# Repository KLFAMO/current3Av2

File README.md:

# current3Av2
Current driver for compensating coils

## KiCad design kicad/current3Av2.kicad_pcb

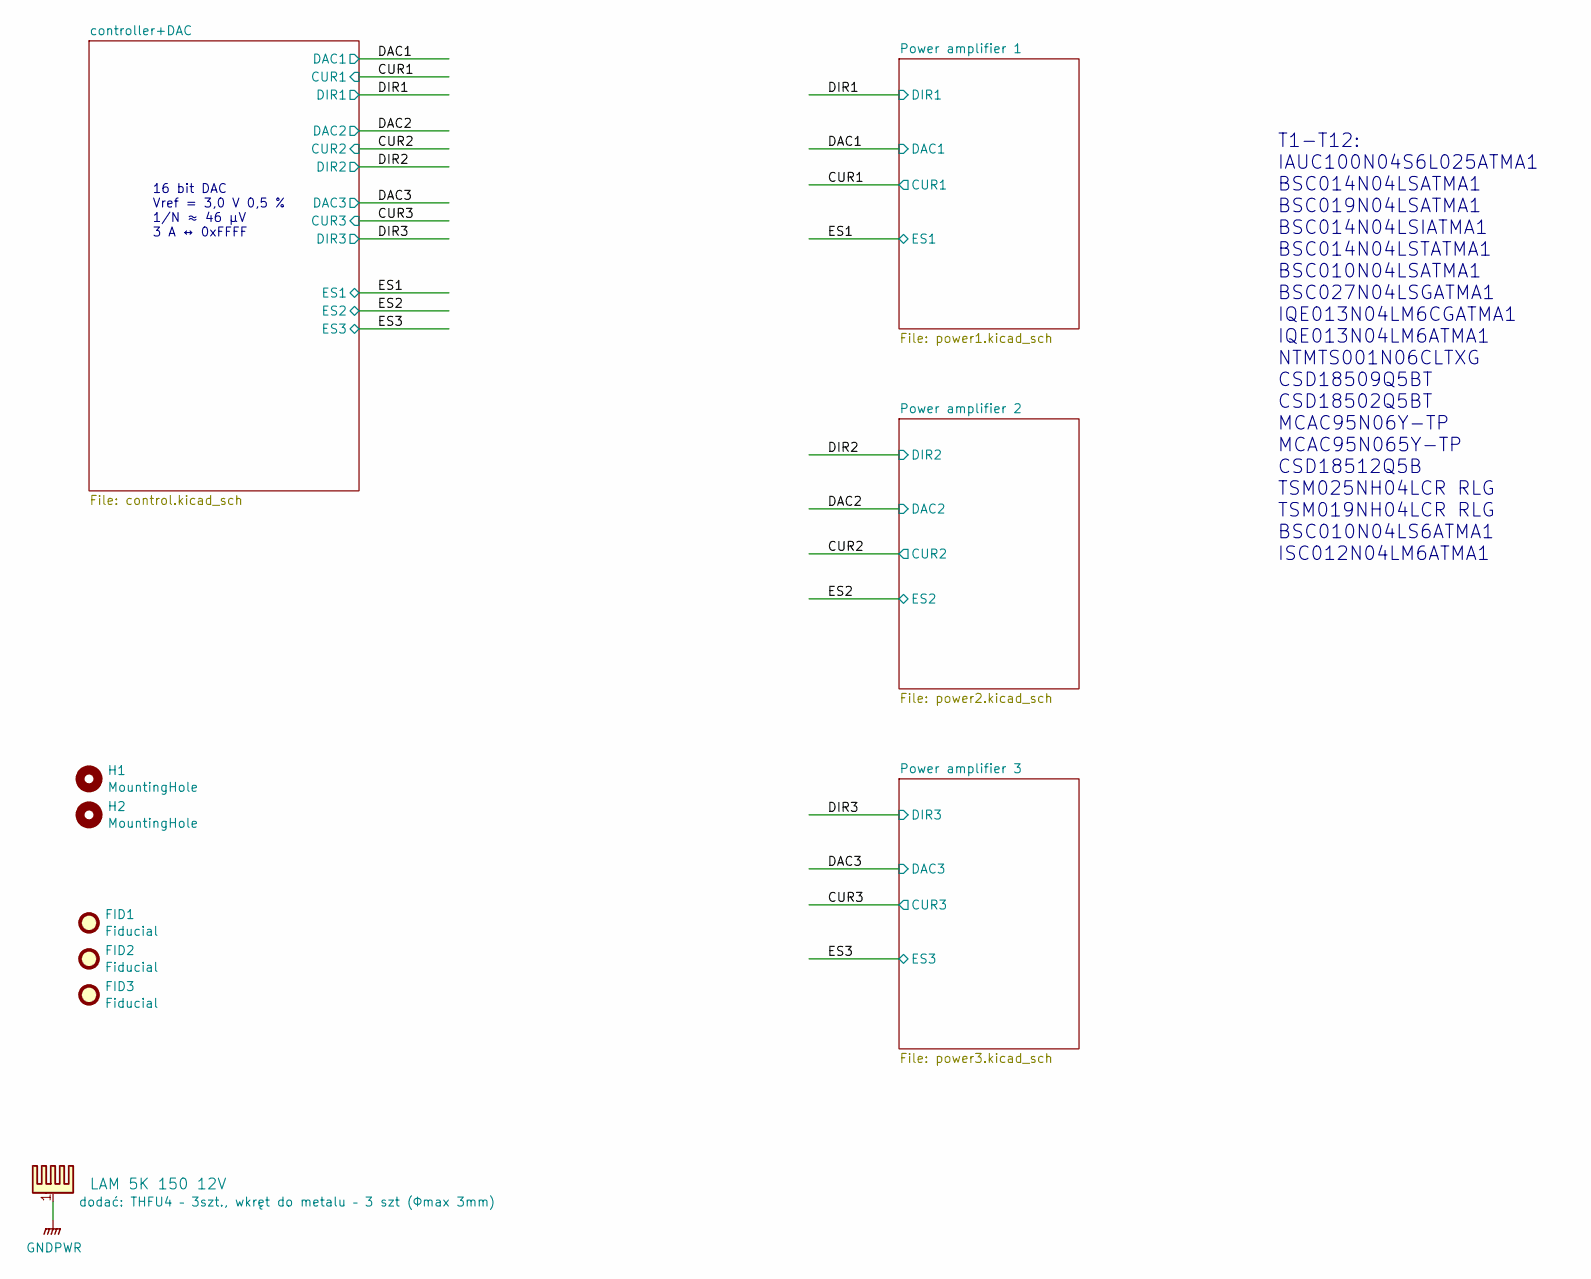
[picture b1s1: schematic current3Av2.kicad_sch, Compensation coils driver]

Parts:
FID1, FID2, FID3: Fiducial; Fiducial_0.5mm_Dia_1mm_Outer
H1, H2: MountingHole; MountingHole_3.2mm_M3_Pad_Via
PD7: LAM 5K 150 12V; Heatsink_50x50x150mm_with_fan_C

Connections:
GND: PD7.1; also elsewhere on the board

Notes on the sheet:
16 bit DAC Vref = 3,0 V 0,5 % 1/N ≈ 46 µV 3 A ↔ 0xFFFF
T1-T12: IAUC100N04S6L025ATMA1 BSC014N04LSATMA1 BSC019N04LSATMA1 BSC014N04LSIATMA1 BSC014N04LSTATMA1 BSC010N04LSATMA1 BSC027N04LSGATMA1 IQE013N04LM6CGATMA1 IQE013N04LM6ATMA1 NTMTS001N06CLTXG CSD18509Q5BT CSD18502Q5BT MCAC95N06Y-TP MCAC95N065Y-TP CSD18512Q5B TSM025NH04LCR RLG TSM019NH04LCR RLG BSC010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

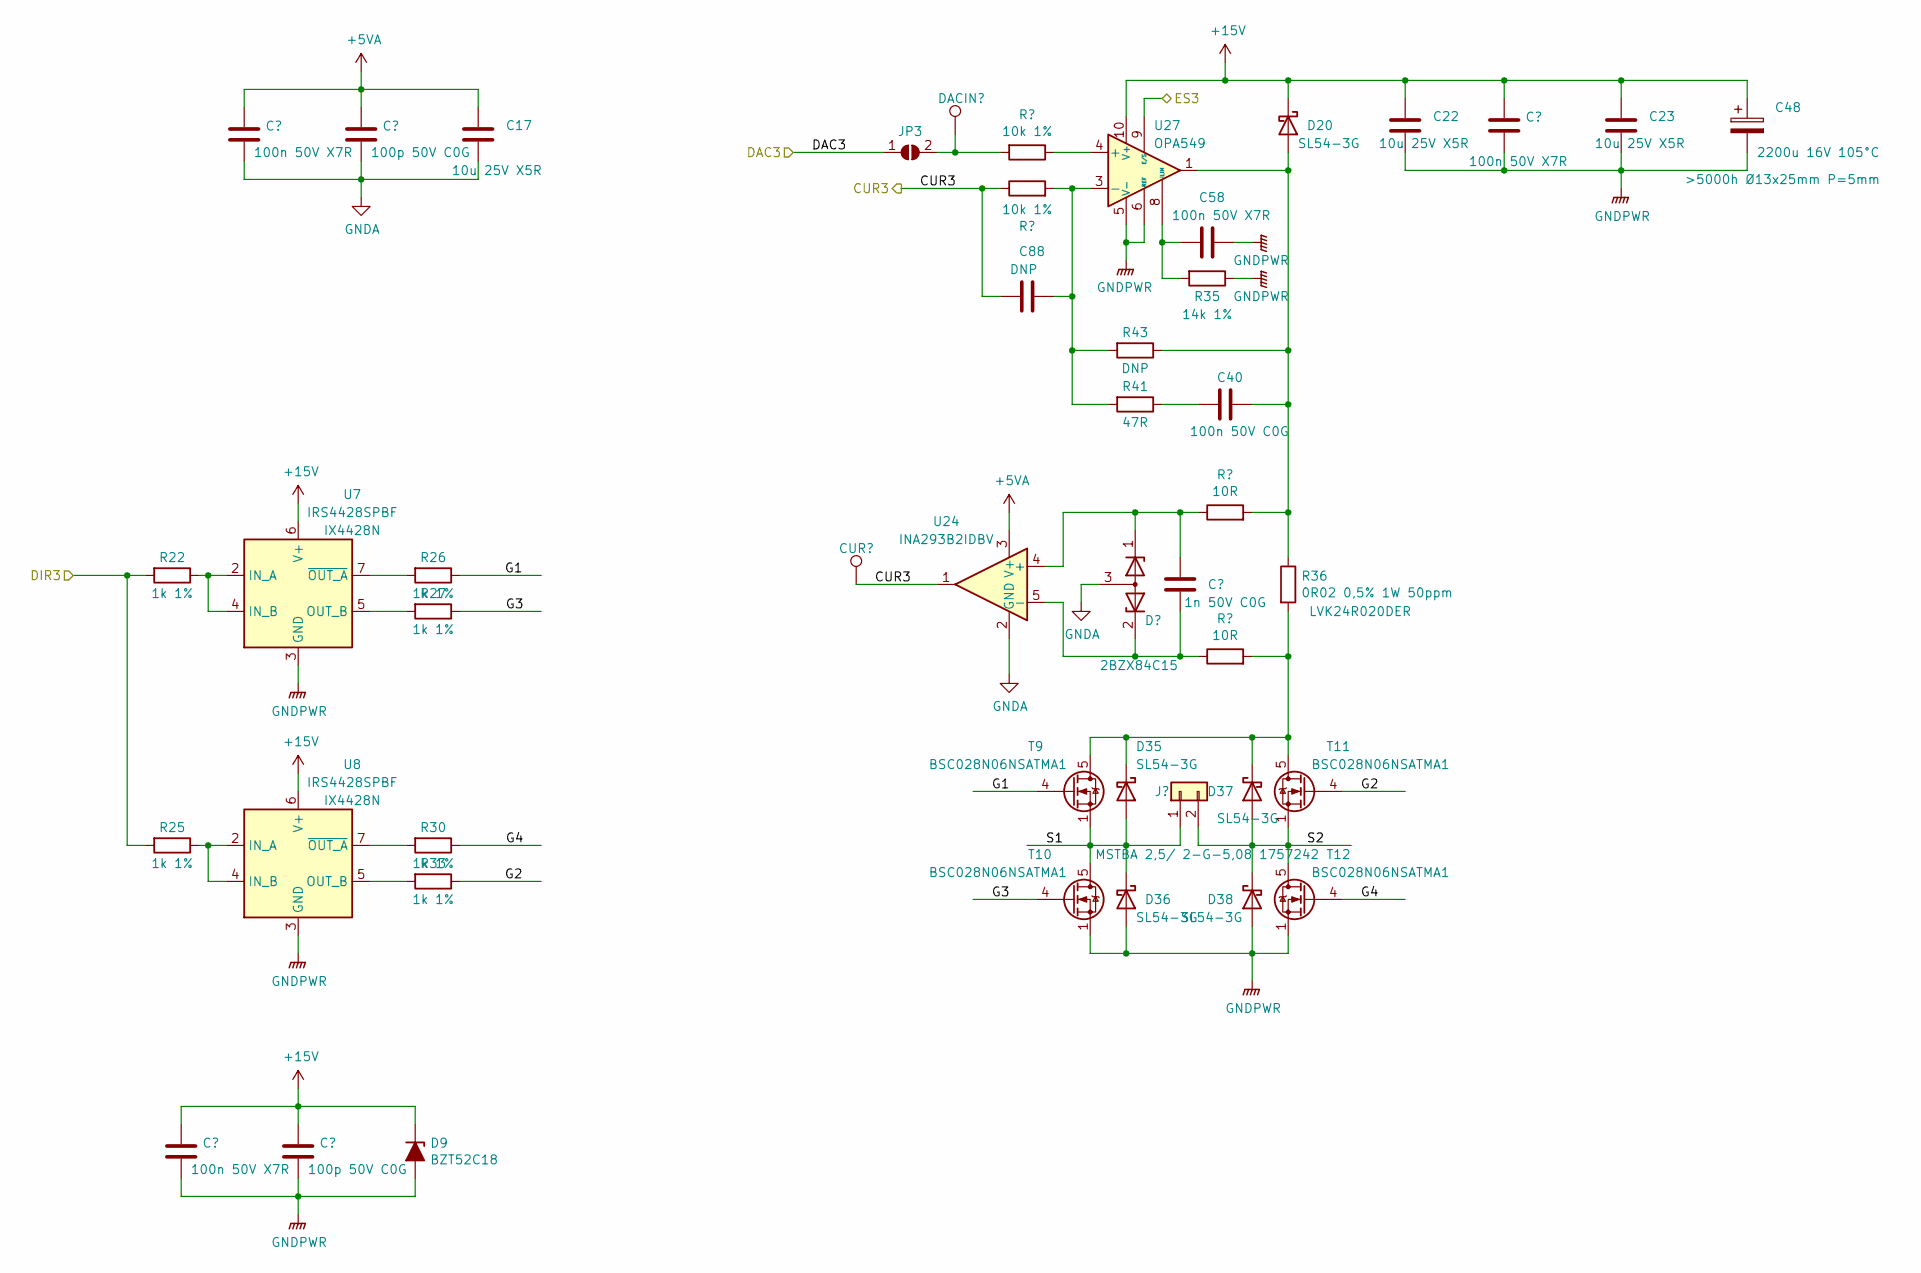
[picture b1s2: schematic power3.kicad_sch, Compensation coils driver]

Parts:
C17, C22, C23: 10u 25V X5R; C_0603
C40: 100n 50V C0G; C_1206
C42, C52, C58, C78: 100n 50V X7R; C_0603
C48: 2200u 16V 105°C; CP_Radial_D14.0mm_P5.00mm
C53, C81: 100p 50V C0G; C_0603
C55: 1n 50V C0G; C_0603
C88: DNP; C_0603
CUR3: TestPoint; Test_Point_THTPad_1.5x1.5mm_Drill0.7mm
D9: BZT52C18; D_SOD-123
D19: 2BZX84C15; SOT-23
D20, D35, D36, D37, D38: SL54-3G; D_SMB
DACIN3: TestPoint; Test_Point_THTPad_1.5x1.5mm_Drill0.7mm
J3: MSTBA 2,5/ 2-G-5,08 1757242; PhoenixContact_MSTBA-G_02x5.08mm_Angled
JP3: SolderJumper_2_Open; GS2_small
R22, R25, R26, R27, R30, R33: 1k 1%; R_0603
R28, R29: 10k 1%; R_0603
R31, R32: 10R; R_0603
R35: 14k 1%; R_0603
R36: 0R02 0,5% 1W 50ppm; R_2512
R41: 47R; R_0805
R43: DNP; R_0805
T9, T10, T11, T12: BSC028N06NSATMA1; TDSON-8-1
U7, U8: IRS4428SPBF; SOIC-8_3.9x4.9mm_Pitch1.27mm
U24: INA293B2IDBV; SOT-23-5
U27: OPA549; TO-220-11_Vertical_StangeredType1_or_not

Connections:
+5VA: C17.1, C52.1, C53.1, U24.3 (V+); also elsewhere on the board
+15V: C22.1, C23.1, C42.1, C48.1, C78.1, C81.1, D9.1 (K), D20.1 (K), U7.6 (V+), U8.6 (V+), U27.10 (V+), U27.11 (V+); also elsewhere on the board
/CUR3: C88.2, CUR3.1, R29.1, U24.1; also elsewhere on the board
/DAC3: JP3.1 (A); also elsewhere on the board
/DIR3: R22.2, R25.2; also elsewhere on the board
/ES3: U27.9 (E/S); also elsewhere on the board
/Power amplifier 3/G1: R26.1, T9.4 (G)
/Power amplifier 3/G2: R33.1, T11.4 (G)
/Power amplifier 3/G3: R27.1, T10.4 (G)
/Power amplifier 3/G4: R30.1, T12.4 (G)
/Power amplifier 3/S1: D35.2 (A), D36.1 (K), J3.1, T9.1 (S), T9.2 (S), T9.3 (S), T10.5 (D)
/Power amplifier 3/S2: D37.2 (A), D38.1 (K), J3.2, T11.1 (S), T11.2 (S), T11.3 (S), T12.5 (D)
GND: C17.2, C22.2, C23.2, C42.2, C48.2, C52.2, C53.2, C58.1, C78.2, C81.2, D9.2 (A), D19.3 (A), D36.2 (A), D38.2 (A), R35.1, T10.1 (S), T10.2 (S), T10.3 (S), T12.1 (S), T12.2 (S), T12.3 (S), U7.3 (GND), U8.3 (GND), U24.2 (GND), U27.5 (V-), U27.6 (REF), U27.7 (V-); also elsewhere on the board
unnamed: C40.1, D20.2 (A), R31.2, R36.1, R43.1, U27.1, U27.2
unnamed: C40.2, R41.1
unnamed: C55.1, D19.2 (K), R32.1, U24.5 (-)
unnamed: C55.2, D19.1 (K), R31.1, U24.4 (+)
unnamed: C58.2, R35.2, U27.8 (ILIM)
unnamed: C88.1, R29.2, R41.2, R43.2, U27.3 (-)
unnamed: D35.1 (K), D37.1 (K), R32.2, R36.2, T9.5 (D), T11.5 (D)
unnamed: DACIN3.1, JP3.2 (B), R28.2
unnamed: R22.1, U7.2 (IN_A), U7.4 (IN_B)
unnamed: R25.1, U8.2 (IN_A), U8.4 (IN_B)
unnamed: R26.2, U7.7 (~OUT_A)
unnamed: R27.2, U7.5 (OUT_B)
unnamed: R28.1, U27.4 (+)
unnamed: R30.2, U8.7 (~OUT_A)
unnamed: R33.2, U8.5 (OUT_B)

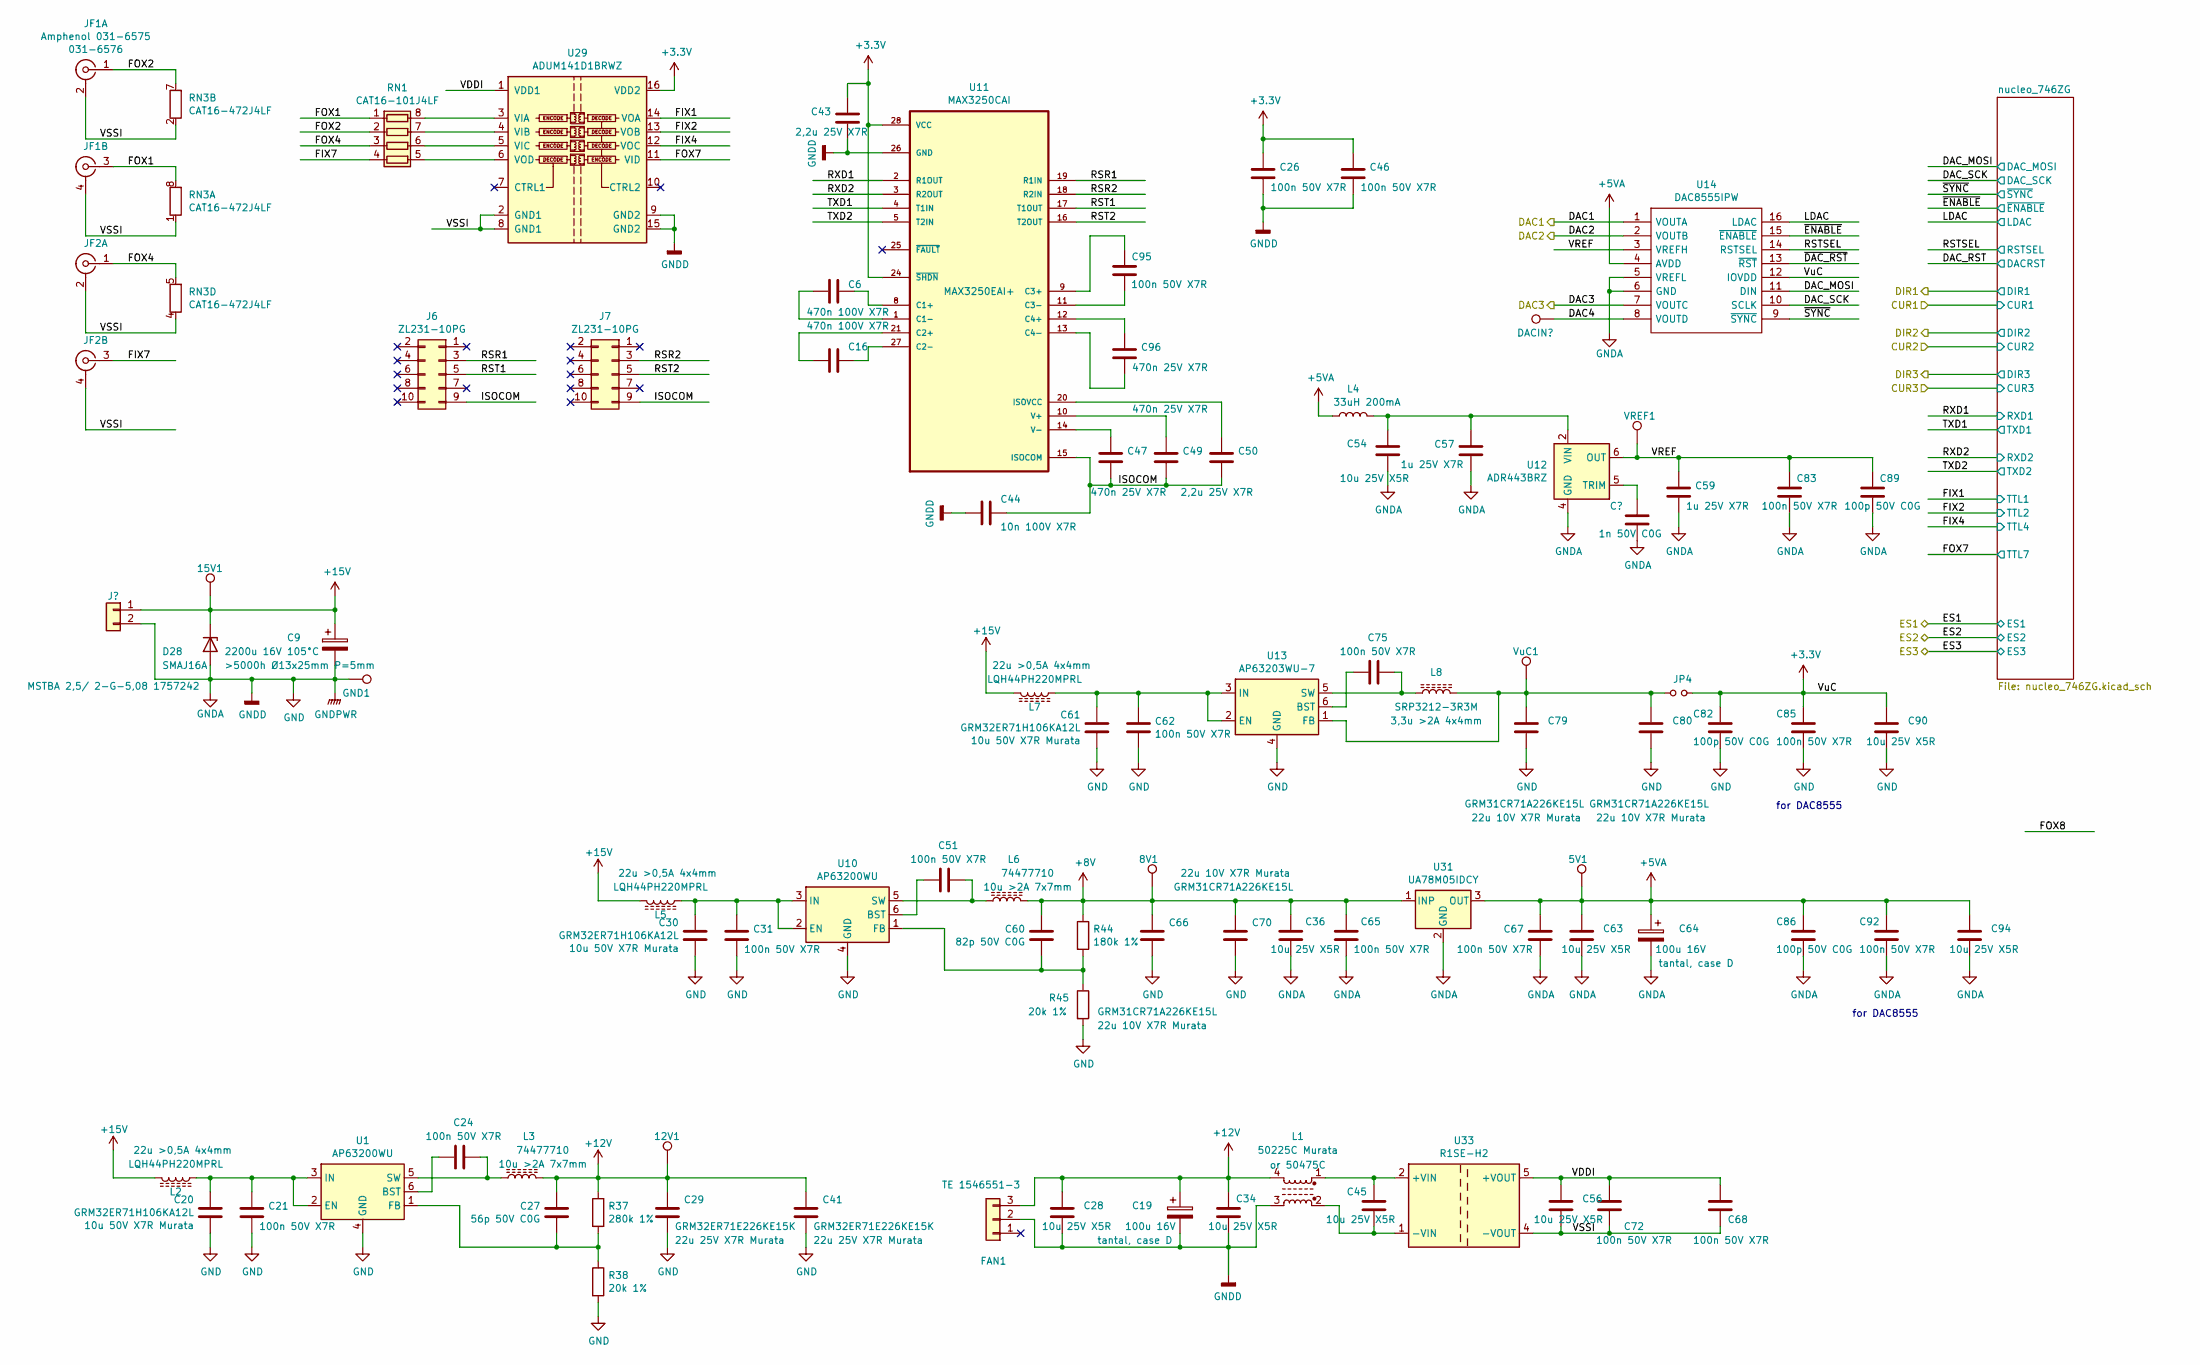
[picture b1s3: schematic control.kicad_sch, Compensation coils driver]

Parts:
5V1, 8V1, 12V1, 15V1: TestPoint; Test_Point_THTPad_1.5x1.5mm_Drill0.7mm
C1: 1n 50V C0G; C_0603
C6, C16: 470n 100V X7R; C_0805
C9: 2200u 16V 105°C; CP_Radial_D14.0mm_P5.00mm
C19, C64: 100u 16V; CP_Tantalum_Case-D_EIA-7343-31_Reflow
C20, C30, C61: GRM32ER71H106KA12L; C_1210
C21, C24, C26, C31, C46, C51, C62, C65, C67, C68, C72, C75, C83, C85, C92, C95: 100n 50V X7R; C_0603
C27: 56p 50V C0G; C_0603
C28, C34, C36, C45, C54, C56, C63, C90, C94: 10u 25V X5R; C_0603
C29, C41: GRM32ER71E226KE15K; C_1210
C43, C50: 2,2u 25V X7R; C_0805
C44: 10n 100V X7R; C_0805
C47, C49, C96: 470n 25V X7R; C_0603
C57, C59: 1u 25V X7R; C_0603
C60: 82p 50V C0G; C_0603
C66, C70, C79, C80: GRM31CR71A226KE15L; C_1206
C82, C86, C89: 100p 50V C0G; C_0603
D28: SMAJ16A; D_SMA
DACIN4: TestPoint; Test_Point_THTPad_1.5x1.5mm_Drill0.7mm
FAN1: TE 1546551-3; TerminalBlock_4UCON_19963_03x3.5mm_Straight
GND1: TestPoint; Test_Point_Bridge_Pitch2.54mm_Drill1.0mm
J4: MSTBA 2,5/ 2-G-5,08 1757242; PhoenixContact_MSTBA-G_02x5.08mm_Angled
J6, J7: ZL231-10PG; IDC-Header_2x05_Pitch2.54mm_Straight
JF1, JF2: Amphenol 031-6575; BNC_Amphenol_031-6575_Horizontal
JP4: Jumper_NO_Small; GS2_small
L1: 50225C Murata; L_CommonMode_Murata_5000
L2, L5, L7: LQH44PH220MPRL; L_MURATA_LQH44
L3, L6: 74477710; L_Wuerth_HCM-7050
L4: 33uH 200mA; L_0805
L8: SRP3212-3R3M; L_Bourns_SRP3212
R37: 280k 1%; R_0603
R38, R45: 20k 1%; R_0603
R44: 180k 1%; R_0603
RN1: CAT16-101J4LF; R_Array_Concave_4x0603
RN3: CAT16-472J4LF; R_Array_Concave_4x0603
U1, U10: AP63200WU; TSOT-23-6
U11: MAX3250CAI; SSOP-28_5.3x10.2mm_Pitch0.65mm
U12: ADR443BRZ; SOIC-8_3.9x4.9mm_P1.27mm
U13: AP63203WU-7; TSOT-23-6
U14: DAC8555IPW; TSSOP-16_4.4x5mm_Pitch0.65mm
U29: ADUM141D1BRWZ; SOIC-16W_7.5x10.3mm_Pitch1.27mm
U31: UA78M05IDCY; SOT-223-3_TabPin2
U33: R1SE-H2; SOIC-5_8-10.7x12.75_Pitch2.54
VREF1: TestPoint; Test_Point_THTPad_1.5x1.5mm_Drill0.7mm
VuC1: TestPoint; Test_Point_THTPad_1.5x1.5mm_Drill0.7mm

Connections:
+5VA: 5V1.1, C63.1, C64.1, C67.1, C86.1, C92.1, C94.1, L4.1, U14.4 (AVDD), U31.3 (OUT); also elsewhere on the board
+8V: 8V1.1, C36.1, C60.1, C65.1, C66.1, C70.1, L6.1, R44.1, U31.1 (INP)
+12V: 12V1.1, C19.1, C27.1, C28.1, C29.1, C34.1, C41.1, FAN1.3, L1.4, L3.1, R37.1
+15V: 15V1.1, C9.1, D28.1 (K), J4.1, L2.2, L5.2, L7.2; also elsewhere on the board
/DAC1: U14.1 (VOUTA); also elsewhere on the board
/DAC2: U14.2 (VOUTB); also elsewhere on the board
/DAC3: U14.7 (VOUTC); also elsewhere on the board
/controller+DAC/DAC4: DACIN4.1, U14.8 (VOUTD)
/controller+DAC/DAC_MOSI: U14.11 (DIN); also elsewhere on the board
/controller+DAC/DAC_SCK: U14.10 (SCLK); also elsewhere on the board
/controller+DAC/FIX1: U29.14 (VOA); also elsewhere on the board
/controller+DAC/FIX2: U29.13 (VOB); also elsewhere on the board
/controller+DAC/FIX4: U29.12 (VOC); also elsewhere on the board
/controller+DAC/FIX7: JF2.3 (In2), RN1.4 (R4.1)
/controller+DAC/FOX1: JF1.3 (In2), RN1.1 (R1.1), RN3.8 (R1.2)
/controller+DAC/FOX2: JF1.1 (In1), RN1.2 (R2.1), RN3.7 (R2.2)
/controller+DAC/FOX4: JF2.1 (In1), RN1.3 (R3.1), RN3.5 (R4.2)
/controller+DAC/FOX7: U29.11 (VID); also elsewhere on the board
/controller+DAC/ISOCOM: C44.1, C47.2, C49.2, C50.2, J6.9, J7.9, U11.15 (ISOCOM)
/controller+DAC/LDAC: U14.16 (LDAC); also elsewhere on the board
/controller+DAC/RSR1: J6.3, U11.19 (R1IN)
/controller+DAC/RSR2: J7.3, U11.18 (R2IN)
/controller+DAC/RST1: J6.5, U11.17 (T1OUT)
/controller+DAC/RST2: J7.5, U11.16 (T2OUT)
/controller+DAC/RSTSEL: U14.14 (RSTSEL); also elsewhere on the board
/controller+DAC/RXD1: U11.2 (R1OUT); also elsewhere on the board
/controller+DAC/RXD2: U11.3 (R2OUT); also elsewhere on the board
/controller+DAC/TXD1: U11.4 (T1IN); also elsewhere on the board
/controller+DAC/TXD2: U11.5 (T2IN); also elsewhere on the board
/controller+DAC/VDDI: C56.1, C68.1, C72.1, U29.1 (VDD1), U33.5 (+VOUT)
/controller+DAC/VREF: C59.1, C83.1, C89.1, U12.6 (OUT), U14.3 (VREFH), VREF1.1
/controller+DAC/VSSI: C56.2, C68.2, C72.2, JF1.2 (Ext1), JF1.4 (Ext2), JF2.2 (Ext1), JF2.4 (Ext2), RN3.1 (R1.1), RN3.2 (R2.1), RN3.4 (R4.1), U29.2 (GND1), U29.8 (GND1), U33.4 (-VOUT)
/controller+DAC/~ENABLE: U14.15 (~ENABLE); also elsewhere on the board
/controller+DAC/~SYNC: U14.9 (~SYNC); also elsewhere on the board
GND: C1.1, C9.2, C19.2, C20.2, C21.2, C26.2, C28.2, C29.2, C30.2, C31.2, C34.2, C36.2, C41.2, C43.2, C44.2, C46.2, C54.2, C57.2, C59.2, C61.2, C62.2, C63.2, C64.2, C65.2, C66.2, C67.2, C70.2, C79.2, C80.2, C82.2, C83.2, C85.2, C86.2, C89.2, C90.2, C92.2, C94.2, D28.2 (A), FAN1.2, GND1.1, J4.2, L1.3, R38.2, R45.2, U1.4 (GND), U10.4 (GND), U11.26 (GND), U12.4 (GND), U13.4 (GND), U14.5 (VREFL), U14.6 (GND), U29.9 (GND2), U29.15 (GND2), U31.2 (GND); also elsewhere on the board
unnamed: C1.2, U12.5 (TRIM)
unnamed: C6.1, U11.8 (C1+)
unnamed: C6.2, U11.1 (C1-)
unnamed: C16.1, U11.27 (C2-)
unnamed: C16.2, U11.21 (C2+)
unnamed: C20.1, C21.1, L2.1, U1.2 (EN), U1.3 (IN)
unnamed: C24.1, L3.2, U1.5 (SW)
unnamed: C24.2, U1.6 (BST)
unnamed: C27.2, R37.2, R38.1, U1.1 (FB)
unnamed: C30.1, C31.1, L5.1, U10.2 (EN), U10.3 (IN)
unnamed: C45.1, L1.1, U33.2 (+VIN)
unnamed: C45.2, L1.2, U33.1 (-VIN)
unnamed: C47.1, U11.14 (V-)
unnamed: C49.1, U11.10 (V+)
unnamed: C50.1, U11.20 (ISOVCC)
unnamed: C51.1, L6.2, U10.5 (SW)
unnamed: C51.2, U10.6 (BST)
unnamed: C54.1, C57.1, L4.2, U12.2 (VIN)
unnamed: C60.2, R44.2, R45.1, U10.1 (FB)
unnamed: C61.1, C62.1, L7.1, U13.2 (EN), U13.3 (IN)
unnamed: C75.1, L8.2, U13.5 (SW)
unnamed: C75.2, U13.6 (BST)
unnamed: C79.1, C80.1, JP4.2, L8.1, U13.1 (FB), VuC1.1
unnamed: C95.1, U11.9 (C3+)
unnamed: C95.2, U11.11 (C3-)
unnamed: C96.1, U11.12 (C4+)
unnamed: C96.2, U11.13 (C4-)
unnamed: RN1.5 (R4.2), U29.6 (VOD)
unnamed: RN1.6 (R3.2), U29.5 (VIC)
unnamed: RN1.7 (R2.2), U29.4 (VIB)
unnamed: RN1.8 (R1.2), U29.3 (VIA)

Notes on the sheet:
for DAC8555

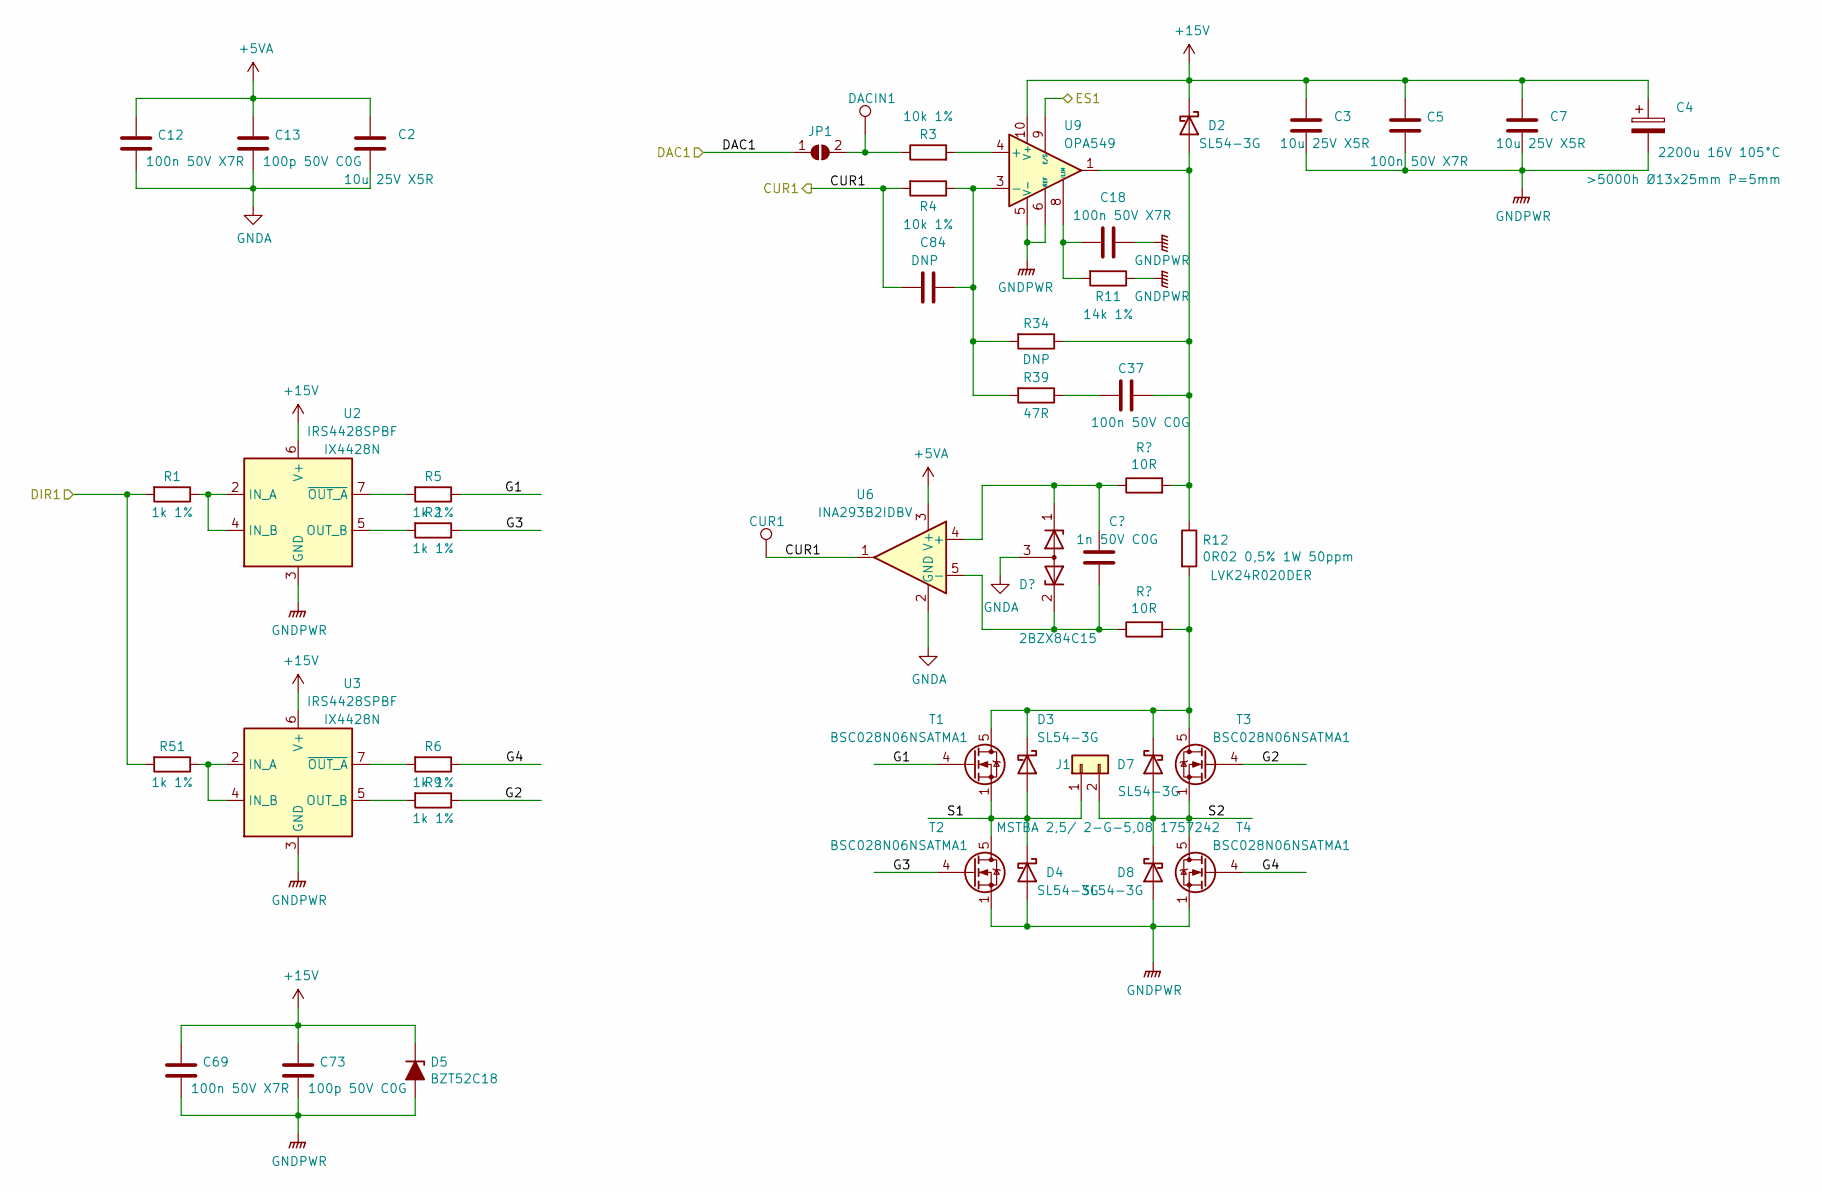
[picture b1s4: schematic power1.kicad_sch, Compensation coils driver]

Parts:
C2, C3, C7: 10u 25V X5R; C_0603
C4: 2200u 16V 105°C; CP_Radial_D14.0mm_P5.00mm
C5, C12, C18, C69: 100n 50V X7R; C_0603
C13, C73: 100p 50V C0G; C_0603
C15: 1n 50V C0G; C_0603
C37: 100n 50V C0G; C_1206
C84: DNP; C_0603
CUR1: TestPoint; Test_Point_THTPad_1.5x1.5mm_Drill0.7mm
D1: 2BZX84C15; SOT-23
D2, D3, D4, D7, D8: SL54-3G; D_SMB
D5: BZT52C18; D_SOD-123
DACIN1: TestPoint; Test_Point_THTPad_1.5x1.5mm_Drill0.7mm
J1: MSTBA 2,5/ 2-G-5,08 1757242; PhoenixContact_MSTBA-G_02x5.08mm_Angled
JP1: SolderJumper_2_Open; GS2_small
R1, R2, R5, R6, R9, R51: 1k 1%; R_0603
R3, R4: 10k 1%; R_0603
R7, R8: 10R; R_0603
R11: 14k 1%; R_0603
R12: 0R02 0,5% 1W 50ppm; R_2512
R34: DNP; R_0805
R39: 47R; R_0805
T1, T2, T3, T4: BSC028N06NSATMA1; TDSON-8-1
U2, U3: IRS4428SPBF; SOIC-8_3.9x4.9mm_Pitch1.27mm
U6: INA293B2IDBV; SOT-23-5
U9: OPA549; TO-220-11_Vertical_StangeredType1_or_not

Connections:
+5VA: C2.1, C12.1, C13.1, U6.3 (V+); also elsewhere on the board
+15V: C3.1, C4.1, C5.1, C7.1, C69.1, C73.1, D2.1 (K), D5.1 (K), U2.6 (V+), U3.6 (V+), U9.10 (V+), U9.11 (V+); also elsewhere on the board
/CUR1: C84.2, CUR1.1, R4.2, U6.1; also elsewhere on the board
/DAC1: JP1.1 (A); also elsewhere on the board
/DIR1: R1.2, R51.2; also elsewhere on the board
/ES1: U9.9 (E/S); also elsewhere on the board
/Power amplifier 1/G1: R5.1, T1.4 (G)
/Power amplifier 1/G2: R9.1, T3.4 (G)
/Power amplifier 1/G3: R2.1, T2.4 (G)
/Power amplifier 1/G4: R6.1, T4.4 (G)
/Power amplifier 1/S1: D3.2 (A), D4.1 (K), J1.1, T1.1 (S), T1.2 (S), T1.3 (S), T2.5 (D)
/Power amplifier 1/S2: D7.2 (A), D8.1 (K), J1.2, T3.1 (S), T3.2 (S), T3.3 (S), T4.5 (D)
GND: C2.2, C3.2, C4.2, C5.2, C7.2, C12.2, C13.2, C18.1, C69.2, C73.2, D1.3 (A), D4.2 (A), D5.2 (A), D8.2 (A), R11.1, T2.1 (S), T2.2 (S), T2.3 (S), T4.1 (S), T4.2 (S), T4.3 (S), U2.3 (GND), U3.3 (GND), U6.2 (GND), U9.5 (V-), U9.6 (REF), U9.7 (V-); also elsewhere on the board
unnamed: C15.1, D1.2 (K), R8.1, U6.5 (-)
unnamed: C15.2, D1.1 (K), R7.1, U6.4 (+)
unnamed: C18.2, R11.2, U9.8 (ILIM)
unnamed: C37.1, D2.2 (A), R7.2, R12.1, R34.1, U9.1, U9.2
unnamed: C37.2, R39.1
unnamed: C84.1, R4.1, R34.2, R39.2, U9.3 (-)
unnamed: D3.1 (K), D7.1 (K), R8.2, R12.2, T1.5 (D), T3.5 (D)
unnamed: DACIN1.1, JP1.2 (B), R3.1
unnamed: R1.1, U2.2 (IN_A), U2.4 (IN_B)
unnamed: R2.2, U2.5 (OUT_B)
unnamed: R3.2, U9.4 (+)
unnamed: R5.2, U2.7 (~OUT_A)
unnamed: R6.2, U3.7 (~OUT_A)
unnamed: R9.2, U3.5 (OUT_B)
unnamed: R51.1, U3.2 (IN_A), U3.4 (IN_B)

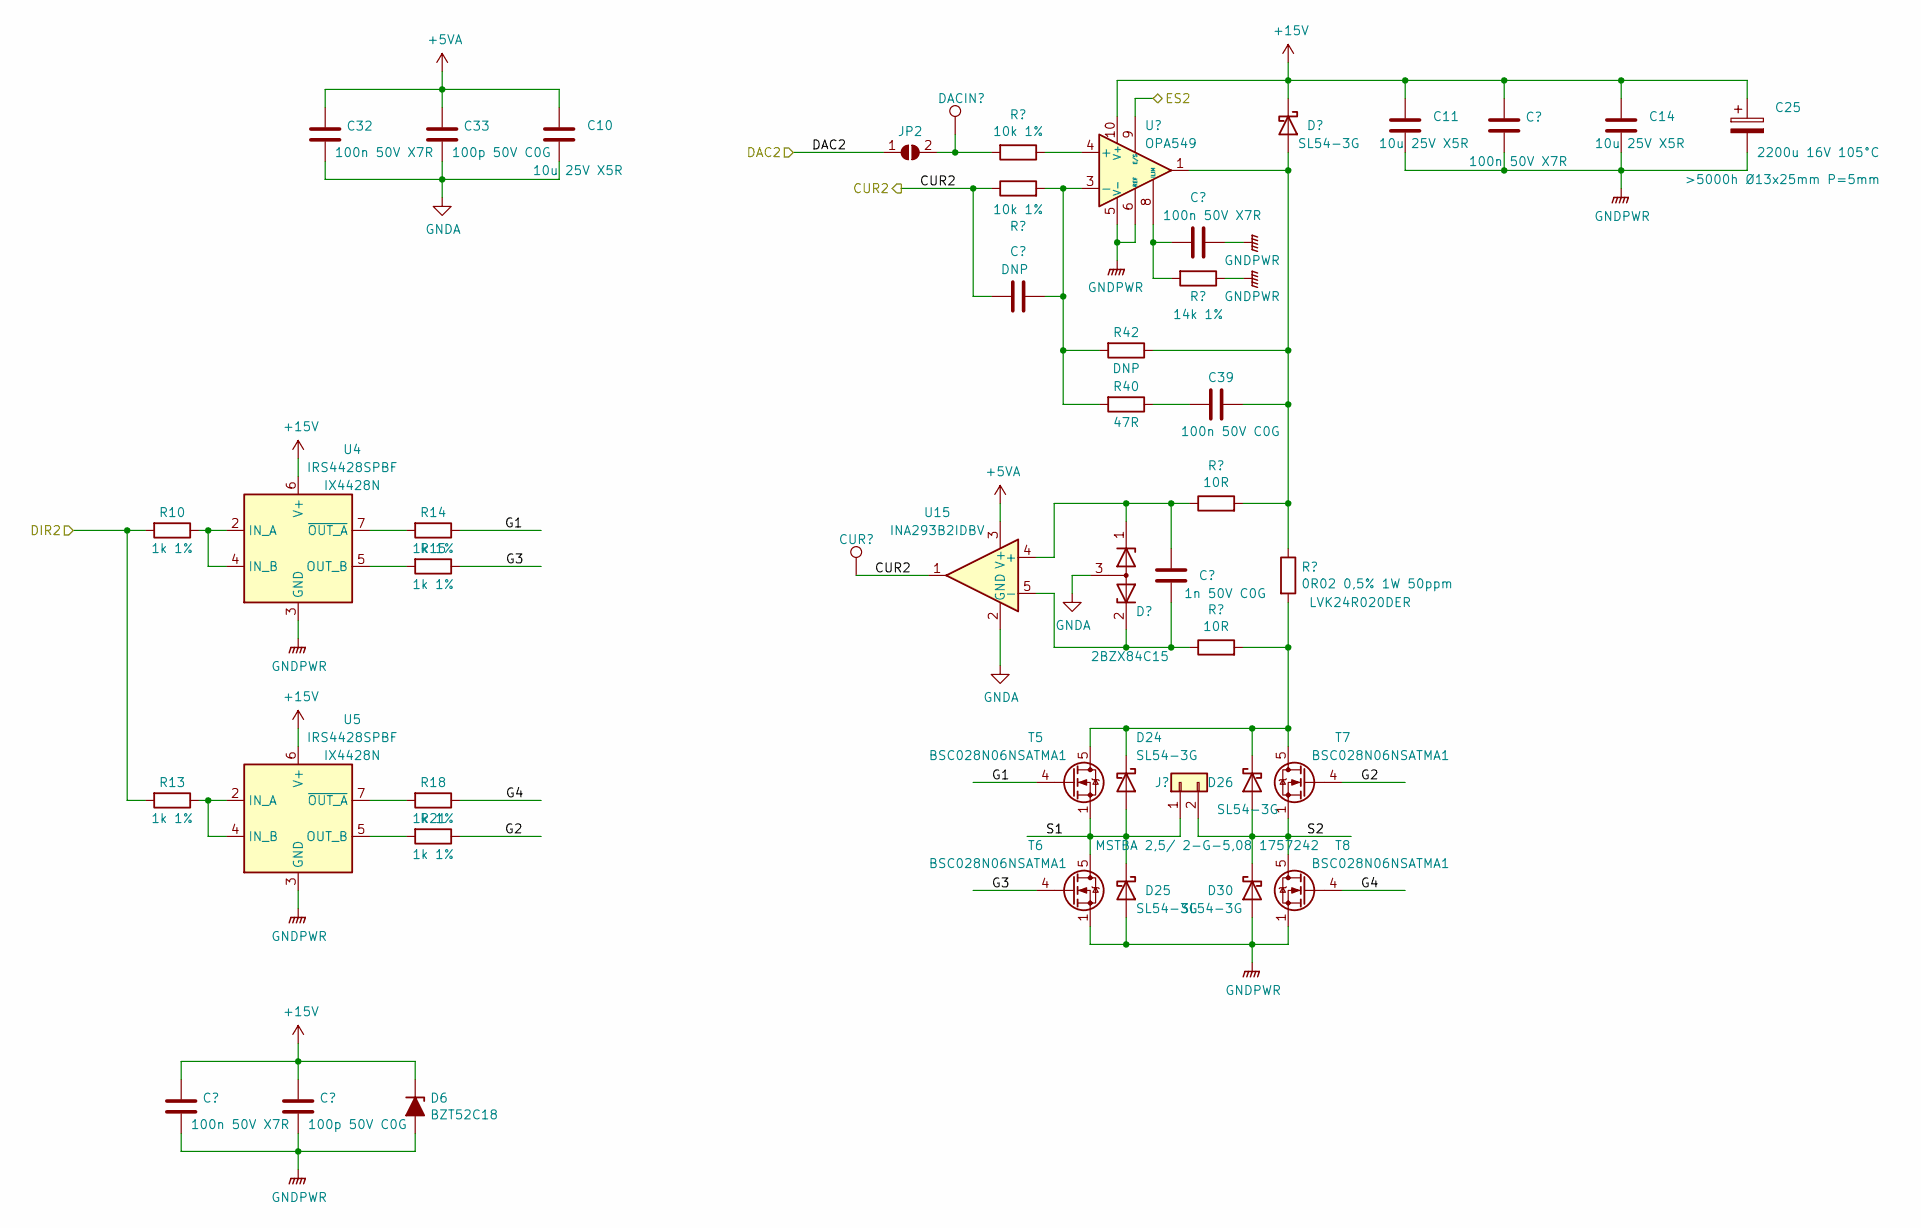
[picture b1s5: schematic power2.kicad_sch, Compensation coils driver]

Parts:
C8, C32, C38, C74: 100n 50V X7R; C_0603
C10, C11, C14: 10u 25V X5R; C_0603
C25: 2200u 16V 105°C; CP_Radial_D14.0mm_P5.00mm
C33, C76: 100p 50V C0G; C_0603
C35: 1n 50V C0G; C_0603
C39: 100n 50V C0G; C_1206
C87: DNP; C_0603
CUR2: TestPoint; Test_Point_THTPad_1.5x1.5mm_Drill0.7mm
D6: BZT52C18; D_SOD-123
D10: 2BZX84C15; SOT-23
D11, D24, D25, D26, D30: SL54-3G; D_SMB
DACIN2: TestPoint; Test_Point_THTPad_1.5x1.5mm_Drill0.7mm
J2: MSTBA 2,5/ 2-G-5,08 1757242; PhoenixContact_MSTBA-G_02x5.08mm_Angled
JP2: SolderJumper_2_Open; GS2_small
R10, R13, R14, R15, R18, R21: 1k 1%; R_0603
R16, R17: 10k 1%; R_0603
R19, R20: 10R; R_0603
R23: 14k 1%; R_0603
R24: 0R02 0,5% 1W 50ppm; R_2512
R40: 47R; R_0805
R42: DNP; R_0805
T5, T6, T7, T8: BSC028N06NSATMA1; TDSON-8-1
U4, U5: IRS4428SPBF; SOIC-8_3.9x4.9mm_Pitch1.27mm
U15: INA293B2IDBV; SOT-23-5
U18: OPA549; TO-220-11_Vertical_StangeredType1_or_not

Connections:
+5VA: C10.1, C32.1, C33.1, U15.3 (V+); also elsewhere on the board
+15V: C8.1, C11.1, C14.1, C25.1, C74.1, C76.1, D6.1 (K), D11.1 (K), U4.6 (V+), U5.6 (V+), U18.10 (V+), U18.11 (V+); also elsewhere on the board
/CUR2: C87.2, CUR2.1, R17.1, U15.1; also elsewhere on the board
/DAC2: JP2.1 (A); also elsewhere on the board
/DIR2: R10.2, R13.2; also elsewhere on the board
/ES2: U18.9 (E/S); also elsewhere on the board
/Power amplifier 2/G1: R14.1, T5.4 (G)
/Power amplifier 2/G2: R21.1, T7.4 (G)
/Power amplifier 2/G3: R15.1, T6.4 (G)
/Power amplifier 2/G4: R18.1, T8.4 (G)
/Power amplifier 2/S1: D24.2 (A), D25.1 (K), J2.1, T5.1 (S), T5.2 (S), T5.3 (S), T6.5 (D)
/Power amplifier 2/S2: D26.2 (A), D30.1 (K), J2.2, T7.1 (S), T7.2 (S), T7.3 (S), T8.5 (D)
GND: C8.2, C10.2, C11.2, C14.2, C25.2, C32.2, C33.2, C38.1, C74.2, C76.2, D6.2 (A), D10.3 (A), D25.2 (A), D30.2 (A), R23.1, T6.1 (S), T6.2 (S), T6.3 (S), T8.1 (S), T8.2 (S), T8.3 (S), U4.3 (GND), U5.3 (GND), U15.2 (GND), U18.5 (V-), U18.6 (REF), U18.7 (V-); also elsewhere on the board
unnamed: C35.1, D10.2 (K), R20.1, U15.5 (-)
unnamed: C35.2, D10.1 (K), R19.1, U15.4 (+)
unnamed: C38.2, R23.2, U18.8 (ILIM)
unnamed: C39.1, D11.2 (A), R19.2, R24.1, R42.1, U18.1, U18.2
unnamed: C39.2, R40.1
unnamed: C87.1, R17.2, R40.2, R42.2, U18.3 (-)
unnamed: D24.1 (K), D26.1 (K), R20.2, R24.2, T5.5 (D), T7.5 (D)
unnamed: DACIN2.1, JP2.2 (B), R16.2
unnamed: R10.1, U4.2 (IN_A), U4.4 (IN_B)
unnamed: R13.1, U5.2 (IN_A), U5.4 (IN_B)
unnamed: R14.2, U4.7 (~OUT_A)
unnamed: R15.2, U4.5 (OUT_B)
unnamed: R16.1, U18.4 (+)
unnamed: R18.2, U5.7 (~OUT_A)
unnamed: R21.2, U5.5 (OUT_B)
